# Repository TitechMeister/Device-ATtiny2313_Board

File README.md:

# Device-ATtiny2313_Board

Meister新歓2024の作業体験に使う基板です。

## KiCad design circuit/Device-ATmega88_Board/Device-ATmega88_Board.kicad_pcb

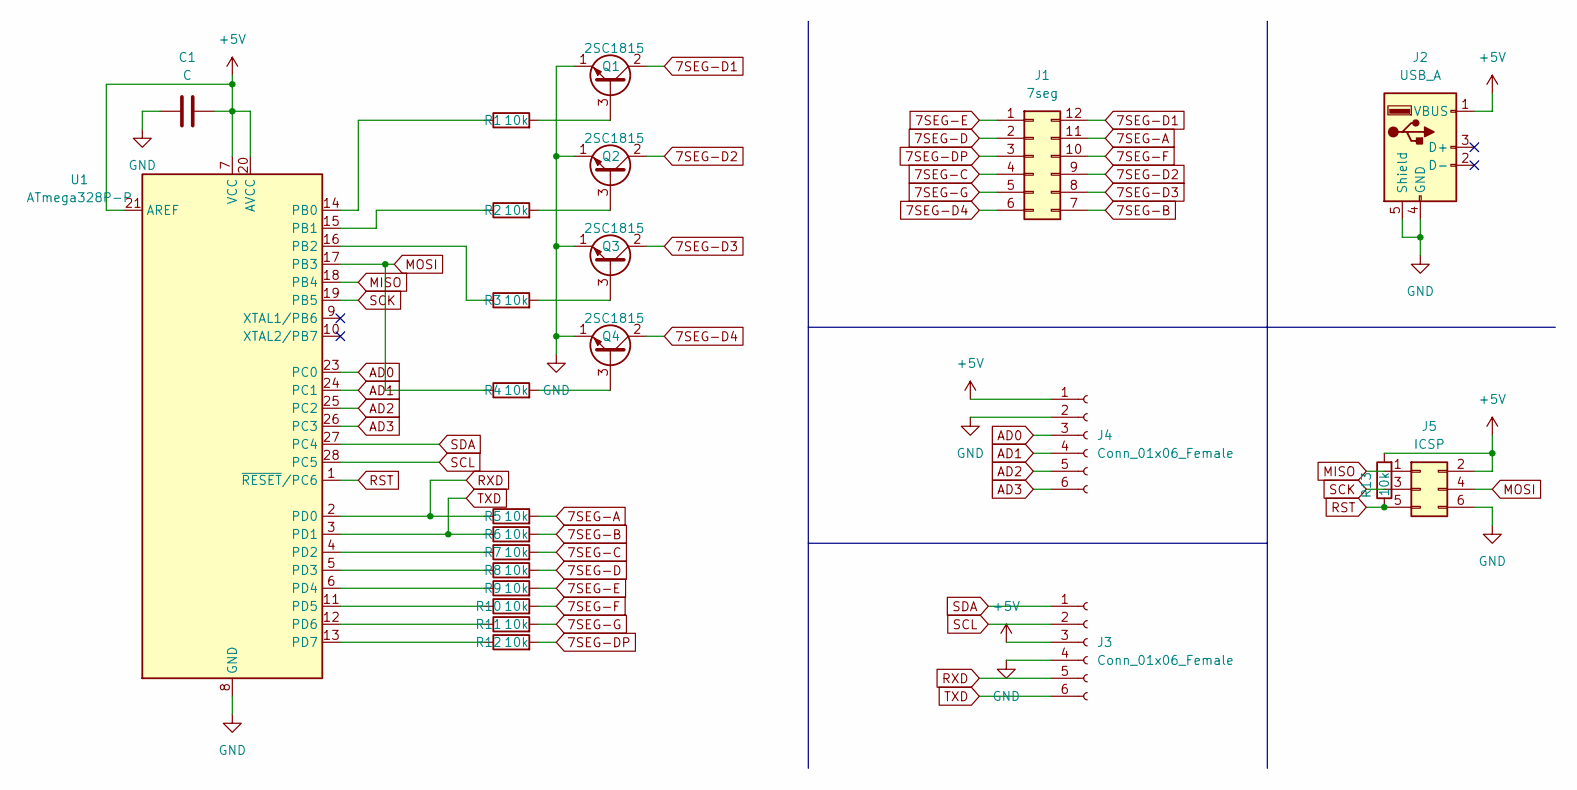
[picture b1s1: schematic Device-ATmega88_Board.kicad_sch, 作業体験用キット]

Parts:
C1: C; C_Disc_D3.0mm_W1.6mm_P2.50mm
J1: 7seg; CA56-12SRWA
J2: USB_A; USB_A_Molex_67643_Horizontal
J3, J4: Conn_01x06_Female; PinSocket_1x06_P2.54mm_Vertical
J5: ICSP; PinHeader_2x03_P2.54mm_Vertical
Q1, Q2, Q3, Q4: 2SC1815; TO-92_Inline
R1, R2, R3, R4, R5, R6, R7, R8, R9, R10, R11, R12, R13: 10k; R_Axial_DIN0207_L6.3mm_D2.5mm_P10.16mm_Horizontal
U1: ATmega328P-P; DIP-28_W7.62mm

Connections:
7SEG-A: J1.11, R5.2
7SEG-B: J1.7, R6.2
7SEG-C: J1.4, R7.2
7SEG-D: J1.2, R8.2
7SEG-D1: J1.12, Q1.2 (C)
7SEG-D2: J1.9, Q2.2 (C)
7SEG-D3: J1.8, Q3.2 (C)
7SEG-D4: J1.6, Q4.2 (C)
7SEG-DP: J1.3, R12.2
7SEG-E: J1.1, R9.2
7SEG-F: J1.10, R10.2
7SEG-G: J1.5, R11.2
+5V: C1.2, J2.1 (VBUS), J3.3, J4.1, J5.2, R13.2, U1.7 (VCC), U1.20 (AVCC), U1.21 (AREF)
AD0: J4.3, U1.23 (PC0)
AD1: J4.4, U1.24 (PC1)
AD2: J4.5, U1.25 (PC2)
AD3: J4.6, U1.26 (PC3)
GND: C1.1, J2.4 (GND), J2.5 (Shield), J3.4, J4.2, J5.6, Q1.1 (E), Q2.1 (E), Q3.1 (E), Q4.1 (E), U1.8 (GND), U1.22 (GND)
MISO: J5.1, U1.18 (PB4)
MOSI: J5.4, R4.1, U1.17 (PB3)
unnamed: Q1.3 (B), R1.2
unnamed: Q2.3 (B), R2.2
unnamed: Q3.3 (B), R3.2
unnamed: Q4.3 (B), R4.2
unnamed: R1.1, U1.14 (PB0)
unnamed: R2.1, U1.15 (PB1)
unnamed: R3.1, U1.16 (PB2)
unnamed: R7.1, U1.4 (PD2)
unnamed: R8.1, U1.5 (PD3)
unnamed: R9.1, U1.6 (PD4)
unnamed: R10.1, U1.11 (PD5)
unnamed: R11.1, U1.12 (PD6)
unnamed: R12.1, U1.13 (PD7)
RST: J5.5, R13.1, U1.1 (~RESET/PC6)
RXD: J3.5, R5.1, U1.2 (PD0)
SCK: J5.3, U1.19 (PB5)
SCL: J3.2, U1.28 (PC5)
SDA: J3.1, U1.27 (PC4)
TXD: J3.6, R6.1, U1.3 (PD1)

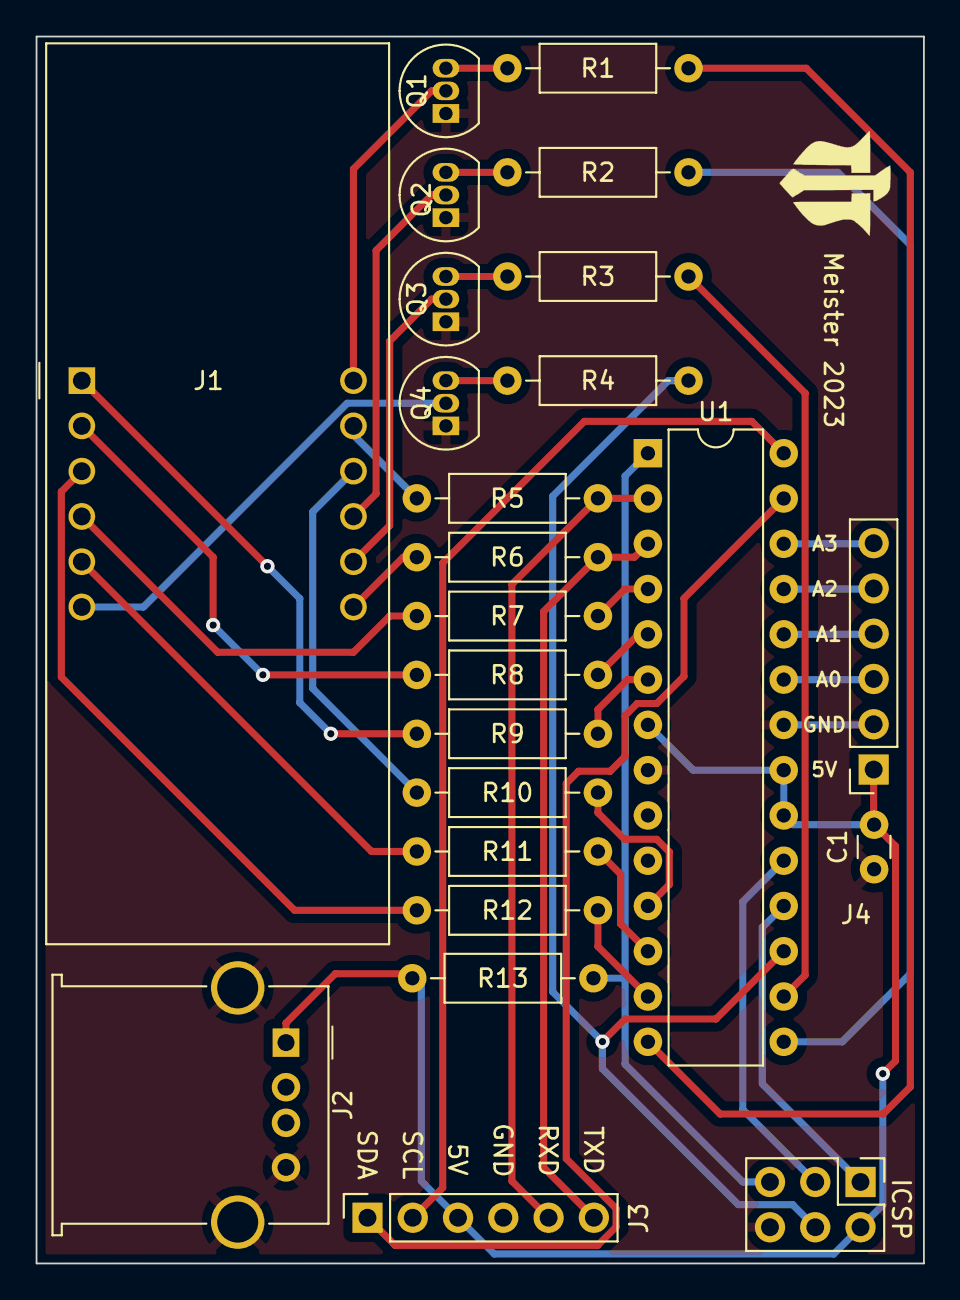
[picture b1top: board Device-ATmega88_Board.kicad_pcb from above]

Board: 2 copper layers, 49.8 x 68.8 mm, 24 parts (0 on the bottom side), 39 nets.

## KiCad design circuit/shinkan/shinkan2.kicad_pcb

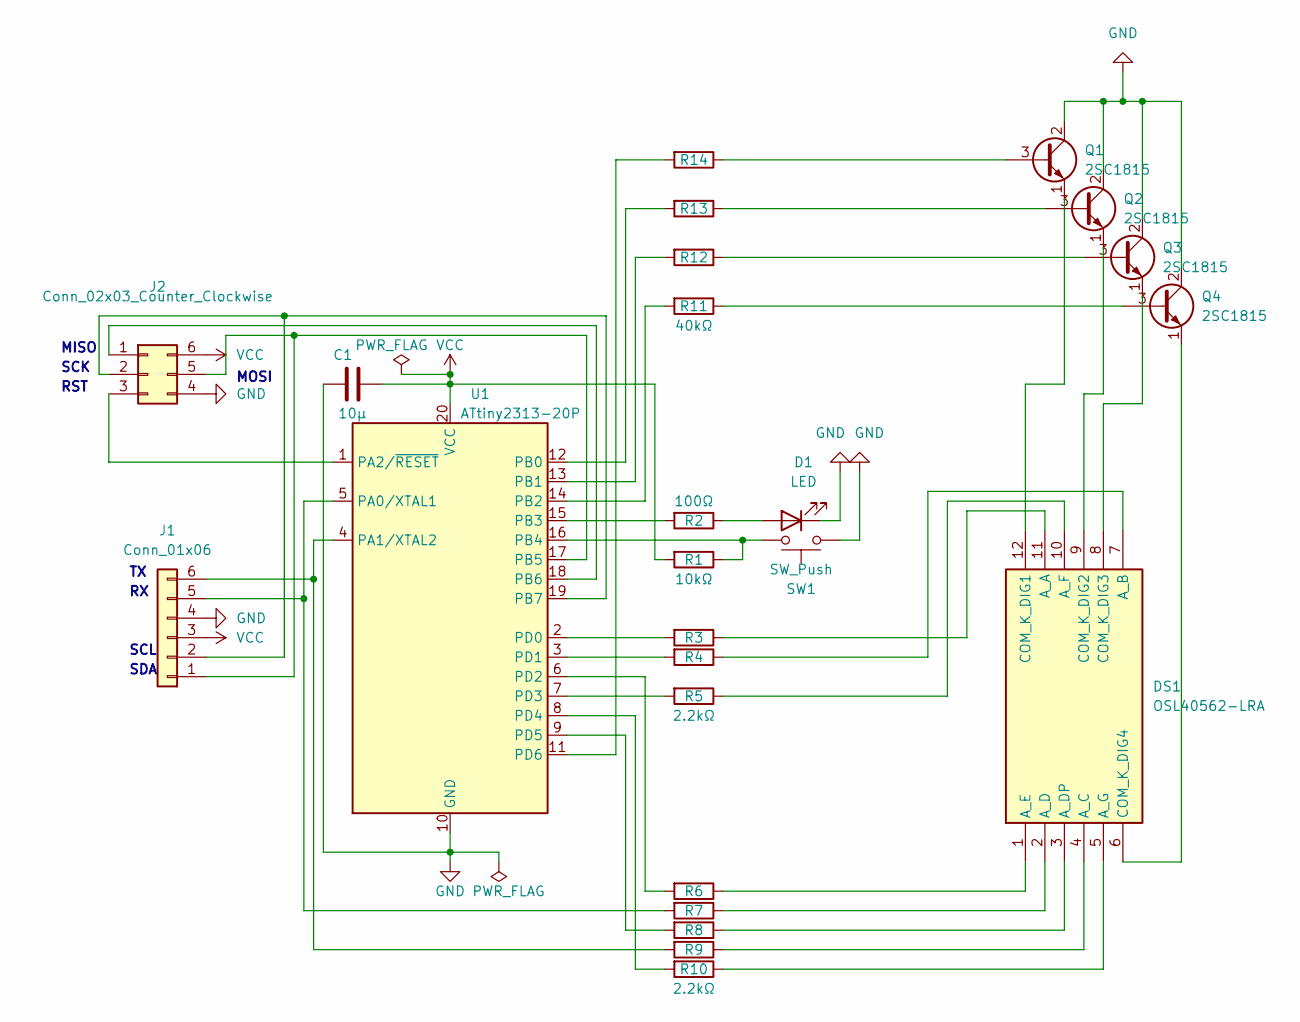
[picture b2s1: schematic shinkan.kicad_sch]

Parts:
C1: 10μ; C_0603_1608Metric
D1: LED; LED_0603_1608Metric
DS1: OSL40562-LRA; DIPS1524W51P254L5035H825Q12N; Manufacturer_Part_Number OSL40562-LRA
J1: Conn_01x06; PinSocket_1x06_P2.54mm_Vertical
J2: Conn_02x03_Counter_Clockwise; PinHeader_2x03_P2.54mm_Vertical
Q1, Q2, Q3, Q4: 2SC1815; TO-92_Inline
R1: 10kΩ; R_0603_1608Metric
R2: 100Ω; R_0603_1608Metric
R3, R4, R5, R6, R7, R8, R9, R10: 2.2kΩ; R_0603_1608Metric
R11, R12, R13, R14: 40kΩ; R_0603_1608Metric
SW1: SW_Push; SW_PUSH_6mm_H8mm
U1: ATtiny2313-20P; DIP-20_W7.62mm

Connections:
GND: C1.2, D1.1 (K), J1.4, J2.4, Q1.2 (C), Q2.2 (C), Q3.2 (C), Q4.2 (C), SW1.1, U1.10 (GND)
unnamed: D1.2 (A), R2.1
unnamed: DS1.11 (A_A), R3.1
unnamed: DS1.7 (A_B), R4.1
unnamed: DS1.4 (A_C), R9.1
unnamed: DS1.2 (A_D), R7.1
unnamed: DS1.3 (A_DP), R8.1
unnamed: DS1.1 (A_E), R6.1
unnamed: DS1.10 (A_F), R5.1
unnamed: DS1.5 (A_G), R10.1
unnamed: DS1.12 (COM_K_DIG1), Q1.1 (E)
unnamed: DS1.9 (COM_K_DIG2), Q2.1 (E)
unnamed: DS1.8 (COM_K_DIG3), Q3.1 (E)
unnamed: DS1.6 (COM_K_DIG4), Q4.1 (E)
unnamed: J1.1, J2.5, U1.17 (PB5)
unnamed: J1.2, J2.2, U1.19 (PB7)
unnamed: J1.5, R7.2, U1.5 (PA0/XTAL1)
unnamed: J1.6, R9.2, U1.4 (PA1/XTAL2)
unnamed: J2.1, U1.18 (PB6)
unnamed: J2.3, U1.1 (PA2/~RESET)
unnamed: Q1.3 (B), R14.1
unnamed: Q2.3 (B), R13.1
unnamed: Q3.3 (B), R12.1
unnamed: Q4.3 (B), R11.1
unnamed: R13.2, U1.12 (PB0)
unnamed: R12.2, U1.13 (PB1)
unnamed: R11.2, U1.14 (PB2)
unnamed: R2.2, U1.15 (PB3)
unnamed: R1.1, SW1.2, U1.16 (PB4)
unnamed: R3.2, U1.2 (PD0)
unnamed: R4.2, U1.3 (PD1)
unnamed: R6.2, U1.6 (PD2)
unnamed: R5.2, U1.7 (PD3)
unnamed: R10.2, U1.8 (PD4)
unnamed: R8.2, U1.9 (PD5)
unnamed: R14.2, U1.11 (PD6)
VCC: C1.1, J1.3, J2.6, R1.2, U1.20 (VCC)

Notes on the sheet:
SCL
MISO
RST
MOSI
SDA
SCK

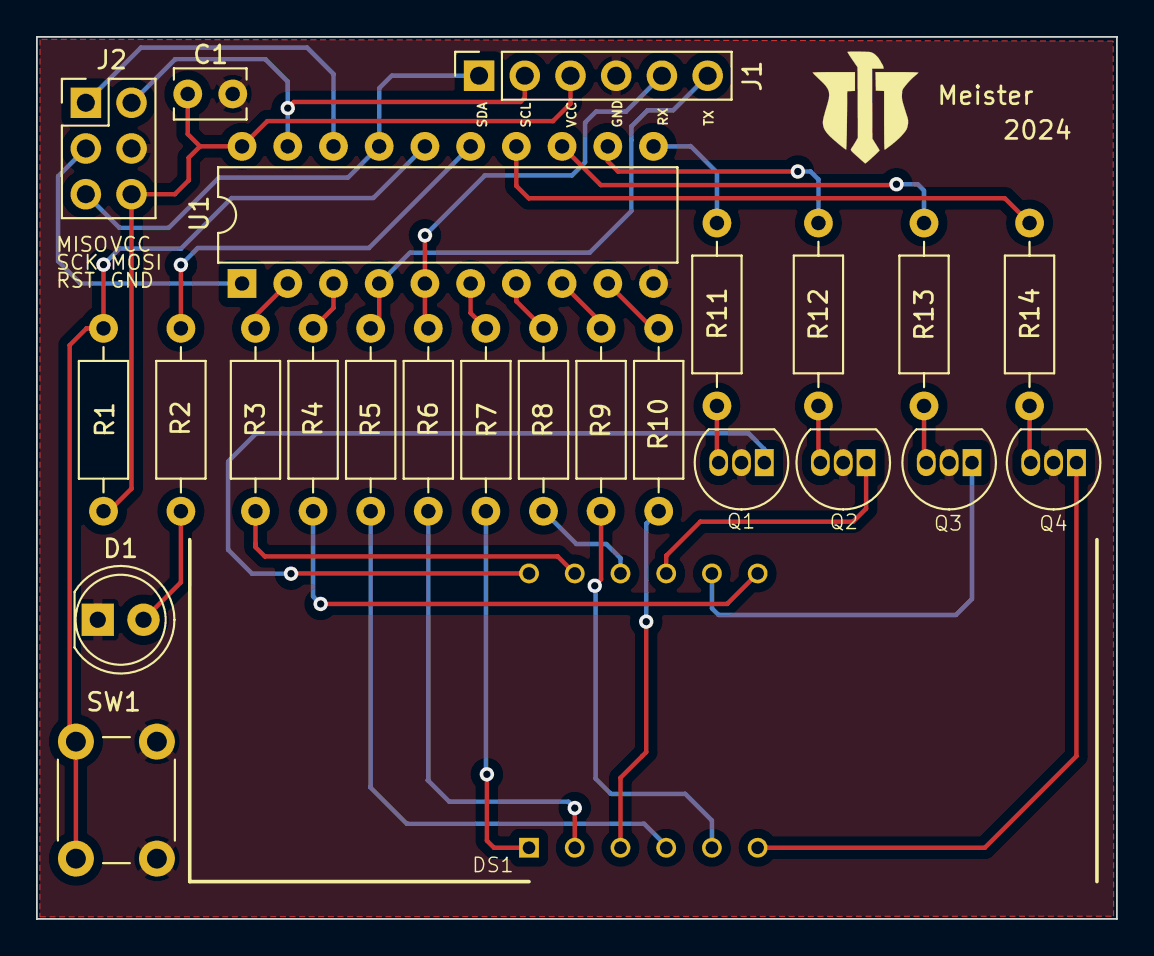
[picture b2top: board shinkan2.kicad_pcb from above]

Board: 2 copper layers, 60.0 x 49.0 mm, 25 parts (0 on the bottom side), 37 nets.

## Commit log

2023-03-31 プログラムを追加
2023-03-31 Remove submodule
2023-03-31 url変更
2023-03-31 編集情報を削除
2023-04-03 day4の記事を修正
2023-04-06 day4の内容を修正
2023-04-06 day5の内容を追加
2023-04-07 数式の表示を調整
2023-04-08 day5の内容を修正
2023-04-10 リンクを修正
2024-04-05 add circuit data
2024-04-09 update day1
2024-04-09 update day2
2024-04-09 update day3
2024-04-09 update day4 and fix day3
2024-04-09 update day 5 & fix day 4
2024-04-10 URLを更新
2024-04-10 fix URL
2024-04-11 fix some things and add title illust
2024-04-15 change timer settings
2024-04-15 fix interrupt vector name
